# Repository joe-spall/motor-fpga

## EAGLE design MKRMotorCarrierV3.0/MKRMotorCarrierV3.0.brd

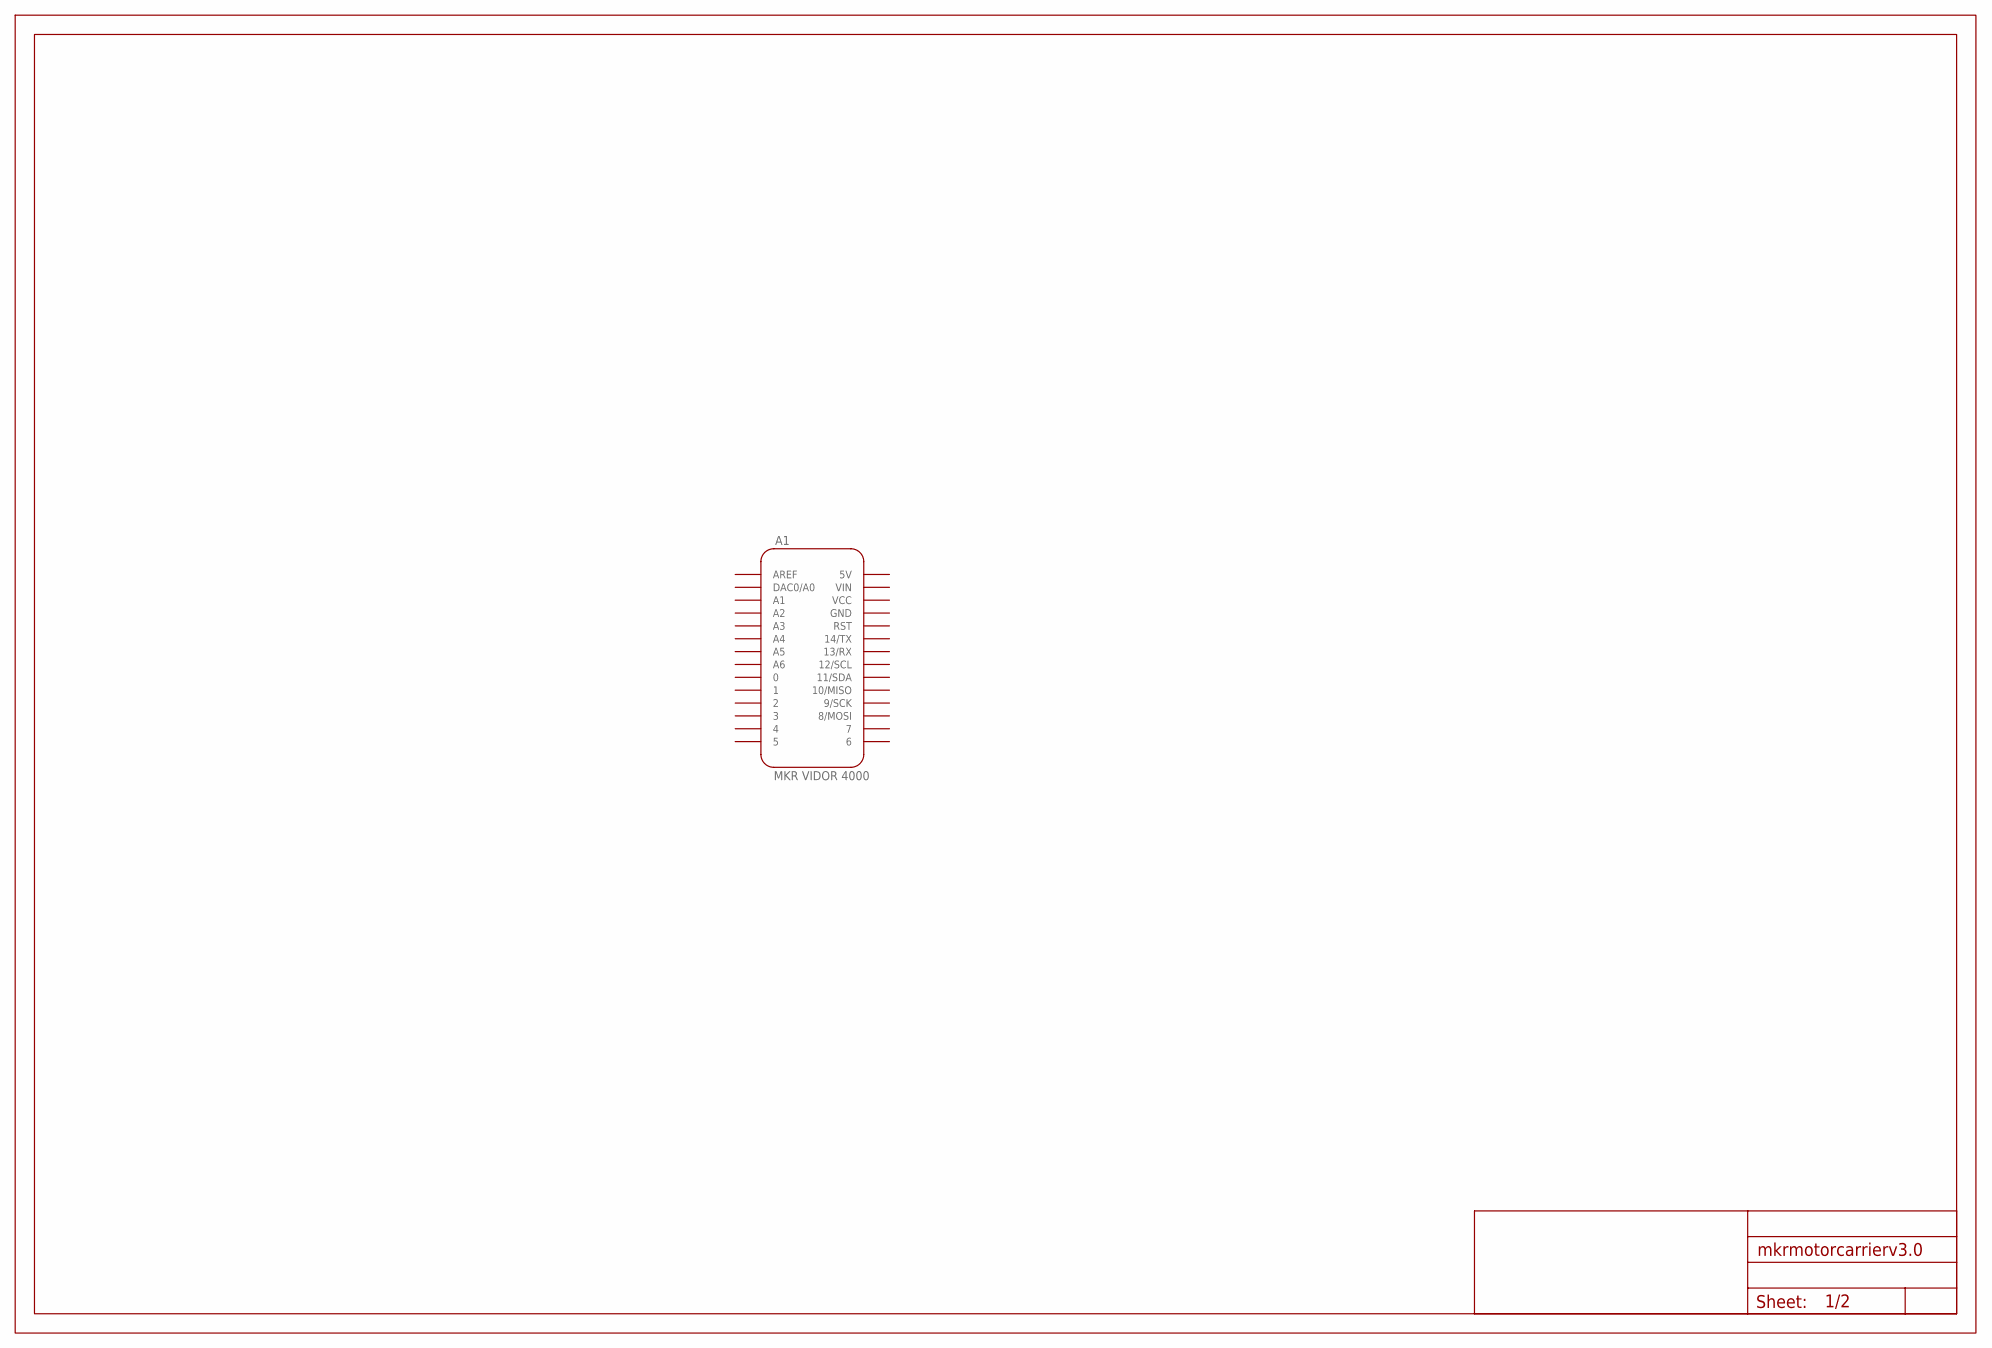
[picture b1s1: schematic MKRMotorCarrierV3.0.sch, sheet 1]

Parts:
A1: MKR VIDOR 4000; BCMI-UTILITY_MKRBOARD
FRAME2: DNP; ARDUINO-UTILITY_FRAME-NO-BAN

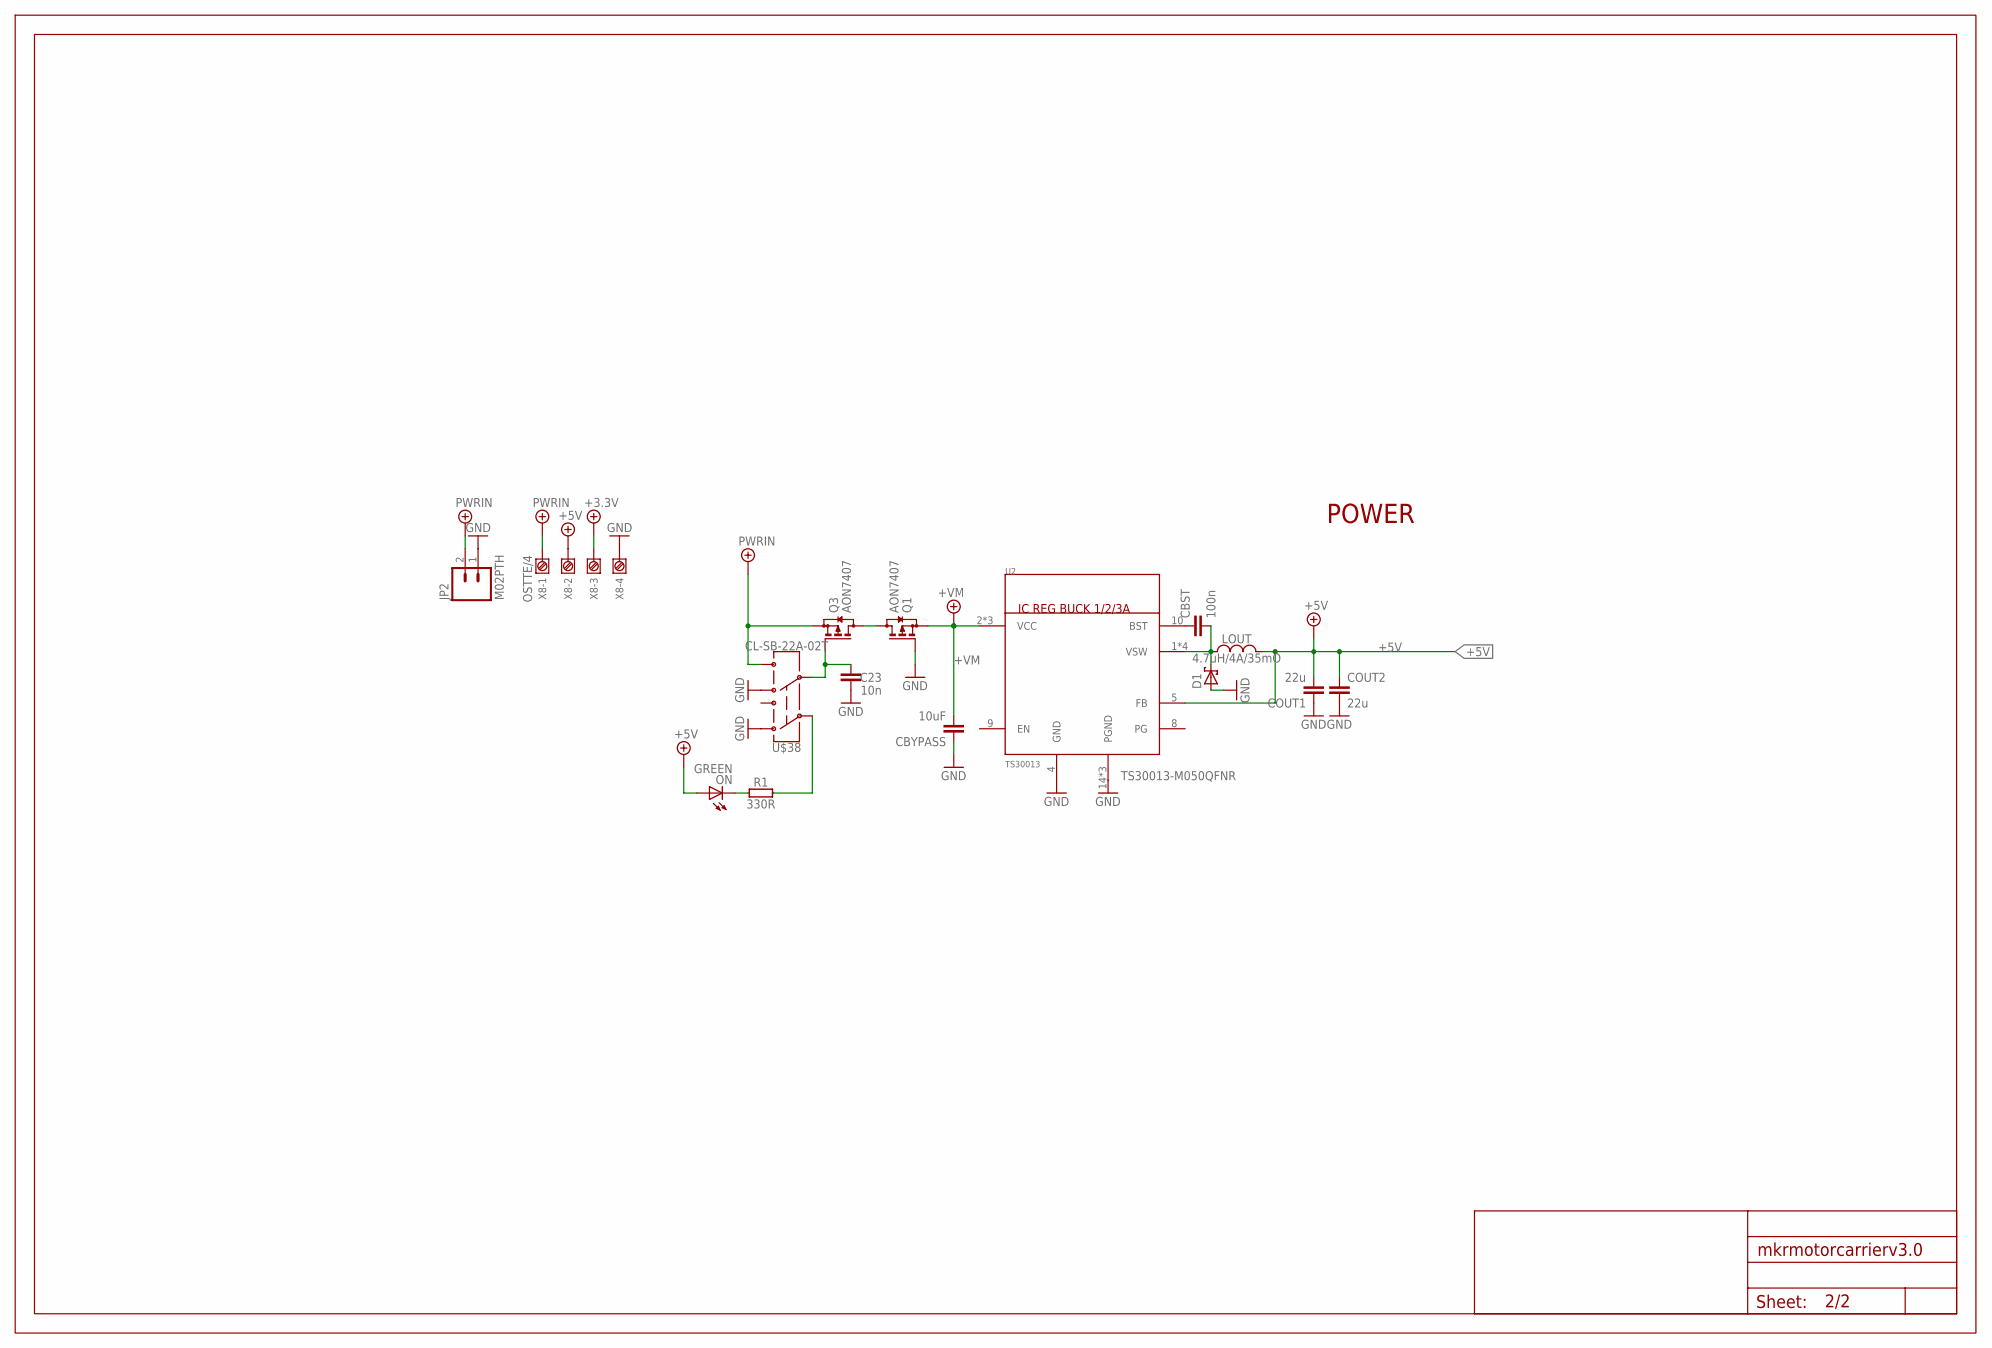
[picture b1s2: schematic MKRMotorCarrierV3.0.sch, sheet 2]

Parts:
C23: 10n; 0402-1005X55N
CBST: 100n; 0402-1005X55N
CBYPASS: 10uF; C1206
COUT1, COUT2: 22u; 0805-R2013X50N
D1: 40V/5A; SOD-128
FRAME1: DNP; ARDUINO-UTILITY_FRAME-NO-BAN
JP2: M02PTH; 1X02
LOUT: 4.7uH/4A/35mO; 6X6_NON-STANDARD
ON: GREEN; LEDC1608X80N-AK
Q1, Q3: AON7407; DFN3X3_8L
R1: 330R; 0402-1005X55N
U2: TS30013; QFN16
U$38: CL-SB-22A-02T; CL-SB-22A
X8: OSTTE/4

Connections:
+3.3V: X8.3
+5V: COUT1.2, COUT2.1, LOUT.P$2 (2), ON.A, U2.5 (FB), X8.2
+VM: CBYPASS.2, Q1.P$1 (S), Q1.P$2 (S), Q1.P$3 (S), U2.2 (VCC), U2.3 (VCC), U2.11 (VCC)
GND: C23.1, CBYPASS.1, COUT1.1, COUT2.2, D1.P$2 (A), JP2.1, Q1.P$4 (G), U2.4 (GND), U2.14 (PGND), U2.15 (PGND), U2.17 (PGND), U$38.P$1 (1), U$38.P$4 (4), X8.4
unnamed: CBST.1, U2.10 (BST)
unnamed: CBST.2, D1.P$1 (C), LOUT.P$1 (1), U2.1 (VSW), U2.12 (VSW), U2.13 (VSW), U2.16 (VSW)
unnamed: R1.2, U$38.P$2 (2)
unnamed: Q1.P$5 (D), Q1.P$6 (D), Q1.P$7 (D), Q3.P$5 (D), Q3.P$6 (D), Q3.P$7 (D)
unnamed: C23.2, Q3.P$4 (G), U$38.P$5 (5)
unnamed: ON.C, R1.1
PWRIN: JP2.2, Q3.P$1 (S), Q3.P$2 (S), Q3.P$3 (S), U$38.P$6 (6), X8.1

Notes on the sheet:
TS30013-M050QFNR
POWER

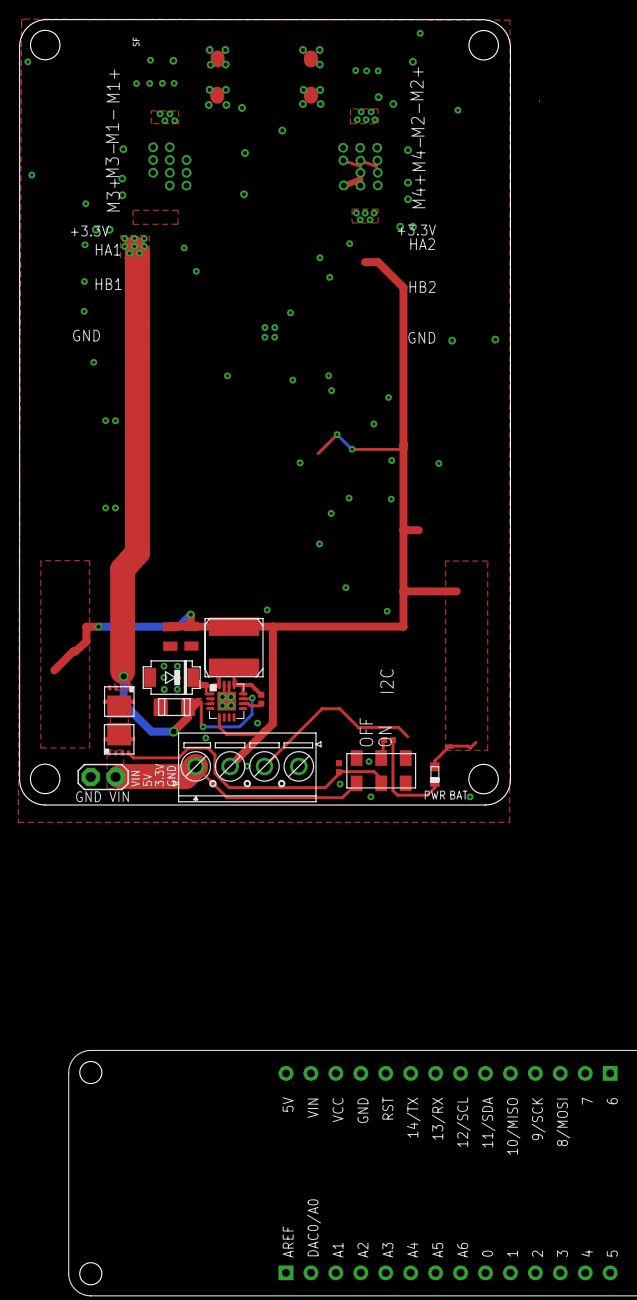
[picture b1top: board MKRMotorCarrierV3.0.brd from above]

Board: 2 copper layers, 53.0 x 80.0 mm, 18 parts (0 on the bottom side), 10 nets.

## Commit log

2020-04-26 Added eagle git ignore
2020-05-13 Made initial setup changes
2020-05-13 Added additional parts to library
2020-05-13 Renamed gitignore
2020-05-13 Revert "Renamed gitignore"
    This reverts commit 54d283ec39a4a1997543f284db2de83d8430d058.
2020-05-14 Continued adding parts

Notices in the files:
parts and their libraries:
BCMI-connectors: Copyright (c) 2016-2017 Arduino LLC.  All right reserved.
